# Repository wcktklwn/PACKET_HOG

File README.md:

# PACKET_HOG

10-node ESP32-C5 scanner carrier board. One master, a bank of scan nodes, single USB-C power in.

Status: **PacketHog-V2 first batch is sold out. A restock order has been placed** (no firm arrival date, no preorders; the store page reopens when boards are in hand). V1 (first batch of 8) is also sold out. Every V2 board is assembled and checked before it ships.

## What it is

Packet Hog C5 is a carrier board built around the Seeed XIAO ESP32-C5. One master node coordinates a bank of scanner nodes over ESP-NOW, each scanning dual-band Wi-Fi (2.4/5 GHz) and BLE. The whole array runs off a single USB-C input.

Built deliberately barebones with power distribution, node bank, antenna breakout, nothing else.

Board size: 183.7mm x 121.1mm (7.23 x 4.77 in), 1.6mm thick. Standard case: 188.1mm x 125.5mm, about 29mm tall. Fan case: about 45.5mm tall.

## Buy it

PacketHog-V2: **$100**, shipping to the US only right now. Same price for every option. **Currently sold out, restock ordered.** Restock alert signup: [tally.so/r/Z9Elga](https://tally.so/r/Z9Elga)

[fusedstamen.com/packethogv2](https://fusedstamen.com/packethogv2)

Options at checkout when available: soldered RP-SMA connectors, or bare board (as received from assembly, SMA positions empty). Every board comes with the standard printed case. A case with a 30mm fan opening is available to print from this repo if you want one. Name and Discord are optional at checkout; I only need a shipping address and email.

Modules (Seeed XIAO ESP32-C5), antennas and fan not included. Outside the US, message me on Discord first - import VAT, duties and carrier fees are paid by the buyer on delivery.

## Case hardware

- Standard case: 4x M3x25 screws into M3 heat-set inserts.
- Fan case lid: 4x M3x40 (about 2.5mm of thread engagement; use M3x45 if it feels loose).
- Fan: 5V, 2-pin, 30mm. Check the fan thickness against the fan case. Fan screws are 2-4x M3x8 to M3x10 self-tapping. Specific fans are untested.

**Note on the RP-SMA connectors (J1-J10):** they're mounted to the board for physical support only - there's no PCB trace routing antenna signal to them. Each node module's signal reaches its SMA connector through a short U.FL-to-RP-SMA pigtail from the module itself, not through the board's copper. Same setup as the Piglet, in case that's caused confusion before.

**Mounting orientation:** every header position follows the same rule. Seat each XIAO module so its USB-C port faces the same side as the nearby capacitor (e.g. C11 sits next to the H1A/H1B pair) - that side matches the direction the onboard USB-C (J11) faces. The module's U.FL antenna pad ends up on the opposite side. Get this backwards and the module won't seat or power on correctly; double check before powering on.

## Version history

- **Prototype 1** - First routed prototype. Had a wiring mistake around the CH224K USB-C PD negotiation chip: on a "smart" PD-negotiating charger, the board could get handed the wrong voltage, which risked damaging the nodes. Safe with plain 5V "dumb" chargers only.
- **Prototype 2** - CH224K removed entirely; replaced with 5.1kΩ pull-down resistors on CC1/CC2, forcing 5V-default behavior regardless of charger. Also added reverse-polarity protection, a fuse at the power input, bulk + per-node decoupling capacitors, and 10 edge-mounted SMA connectors for external antennas. Had a layout flaw: SMA connector mounts sat too close to the header pins, leaving insufficient clearance to hand-solder/route pigtail connections without crowding the header footprints. Also shipped without mounting holes, so boards couldn't be securely fastened into a case.
- **PacketHog-V1** - Fixes the clearance flaw by widening the board (77.1mm to 121.1mm) to give proper spacing between the SMA connectors and the header rows. Added M3 mounting holes. Rounded board corners. SMA connectors hand-soldered (not PCBA-populated). First batch of 8 sold out.
- **PacketHog-V2** - Current revision. Power traces widened from 0.5mm to 1.0mm (the USB-C-to-fuse run is limited by the connector pad width). Added a 2-pin fan header (5V + GND, factory assembled). Added an AUX 5V/GND through-hole header, unpopulated, same pinout as the fan header (square pad GND, round pad +5V). Added 7 labelled test points: USB input voltage, between fuse and diode, 5V rail, far-end 5V, and 3x GND. Silkscreen cleanup; back label says V2. Power parts unchanged from V1. Still hand-soldered through-hole RP-SMA (mechanical only), plain USB-C 5V with no PD, 3A maximum (PTC fuse, fan counts against it).
- **Planned for V3** - Power switch, power LED, onboard U.FL plus edge SMA, battery input, possibly 4-layer.

**Known issue:** some nodes drop out with certain off-brand USB cables or power banks. Cause not yet measured; V2 does not claim to fix it. Use a decent USB-C cable and a supply that can deliver 5V at 3A.

## PacketHog-20

Unreleased 20-socket layout in `hardware/PacketHog-20/`. PacketHog-V2 above is unchanged and is still the board for sale. This board has not been fabricated or powered.

20 XIAO ESP32-C5 sockets, 2 rows of 10. Nodes 1–10 run along the top edge and 11–20 along the bottom, on the same 35 mm SMA pitch as V2. Board size: 432.05 mm × 86.10 mm (17.01 × 3.39 in), 1.6 mm thick, 2-layer, 1 oz. Corners are rounded at a 3 mm radius. The V2 case does not fit, and there is no case for this board. Seat each module the same way as V2: USB-C toward the nearby capacitor, the same direction the board USB connector (J21) faces. V2 fits a U.FL beside each SMA and a short trace between the center pins. This board leaves that connector and that trace off. The antenna is still the module's own U.FL and a pigtail to the SMA.

The USB-C input is the V2 circuit, shifted to the right edge: 5.1 kΩ on CC1/CC2, series Schottky, PTC fuse. That path cannot feed 20 radios. The high-current input is J22, a Phoenix MKDS 1,5/2-5.08 screw terminal on the left. Square pad is GND, round pad is VIN, and the wire openings face the board edge. F2 is a Littelfuse 0451010, a 10 A very-fast Nano2 fuse, in series with Q1, an onsemi NTMFS002P03P8Z P-channel MOSFET. Its Rds(on) maximum is 2.3 mΩ at Vgs = −4.5 V, about 18 mV and 0.15 W at 8 A using that datasheet maximum. The package is CASE 506EZ. The footprint on the board is the library SO-8 FL land ONSemi_SO-8FL_488AA, which matches the 506EZ recommended land. The exposed drain pad is not a hand-solder package.

Q2, an MMBT3904, pulls the gate down only while the fused input is present, so the FET turns on for the screw terminal and stays off when only USB is connected. USB then cannot backfeed into J22, and the USB Schottky stays reverse-biased while the FET drop is tens of millivolts. D4, a BZT52C12, clamps the gate-source voltage. It does not clamp the input. The body diode and the channel both pass a higher VIN onto the 5 V rail. The silk says 5V ONLY. A 12 V supply on J22 would destroy the modules. Reverse polarity on J22 leaves the FET off.

The screw terminal, the USB input, and the buck share an unswitched +5V island. On the back of the inlet that tie is 2.8 mm. It has not been measured at the array current. Q7, another NTMFS002P03P8Z, connects the island to the load net. Its source is the island and its drain is the load, so the body diode does not run the radios when the FET is off. From there a 2.8 mm spine feeds a 4.0 mm bus along the top, ending at x = 419.50 mm, and a 3.2 mm bus along the bottom, from the bulk capacitor at x = 77.70 mm to x = 413.50 mm. A rough IPC-2221 figure for 10 A on 1 oz external copper at a 20 °C rise is about 4.6 mm, and the spine stays 2.8 mm because the header pins sit next to it. An estimate of simultaneous transmit, about 0.44 A per node at 5 V, is about 8.9 A. The spine and the 8 A buck below are sized under that estimate. An average scan is far below simultaneous transmit. None of this drop or heating has been measured.

SW1 is a C&K JS202011CQN, a maintained DPDT slide switch. One pole grounds Q7's gate in the ON position. R23, 100 kΩ to the island, holds the gate up when that pole is open, so the FET stays off. The other pole grounds the base of Q8, an MMBT3904, in the ON position. When the switch is open, R22, 100 kΩ from the pack, turns Q8 on and holds the buck enable low. The switch carries gate and base current, not the radio current. Charging stays on the fused input and continues while the radios are off. USB is on the island side of Q7, so the board USB does not run the radios with the switch open either. The silk says ON on the wired throw. The C&K pin drawing was not available, so that direction has not been checked. If the slider is backwards, both positions still exist and the silk names the one that is wired on. Q7 uses the same 2.3 mΩ maximum, about 18 mV and 0.15 W at 8 A from that datasheet figure. That drop has not been measured. The switch does not clamp the input. The inlet silk still says 5V ONLY.

The pack is external: a 2S Li-ion pack with its own BMS, plugged into J23, an XT30PW-M. Onboard 18650 holders were rejected. One cell cannot supply the array at 5 V, and a holder adds reverse insertion and height. Library silk marks J23 pad 2 as + and pad 1 as −. That marking is the library silk and has not been checked against the AMASS drawing. Confirm it before building a cable. J24 is a JST XH B3B-XH-A balance header. Pin 1 is pack−, pin 2 is the mid-cell sense, and pin 3 is cell+ on the cell side of Q3, the same node as J23 pad 2. The balance plug is a sense connection for the charger. It is not pack protection, and pin 3 must stay on the cell side of Q3 so the cable does not bypass the reverse-polarity FET.

Q3, another NTMFS002P03P8Z, has its drain toward the pack and its source on the protected PACK rail. A reversed pack leaves the FET off. A correct pack bootstraps through the body diode and the FET turns on. This does not clamp the pack voltage.

U1 is an Injoinic IP2326 boost charger. It charges the pack from the fused screw-terminal input (VIN_F). With the adapter unplugged the charger input is open, so the buck cannot feed the charger. Charge current is about 1 A (90.9 kΩ on ISET). The charge timer is 12 h (120 kΩ on TIME_SET), so a larger pack can hit the timeout and stop early. The NTC pin is a fixed 51 kΩ to ground, not a cell thermistor. CON_SEL and VSET are open, which selects 2S and 8.4 V. The datasheet application note's series 0.5 Ω on VIN is omitted, and so is the balance-bleed resistor. The pack BMS does the balance bleed. A 1 A charge into 2S is on the order of 2 A from the 5 V input. That current shares F2 with the radios. Full transmit while charging sits at the 10 A hold rating of the fuse.

U2 is a TI TPS56837 8 A synchronous buck, 500 kHz, set to about 5.0 V (73.2 kΩ / 10.0 kΩ). Q4 connects the buck onto the unswitched island through another P-channel FET, and Q5 holds the buck off while the adapter is present, so the adapter runs the radios and the charger fills the pack. Q8 does that same hold from the pack while SW1 is open, so an unloaded buck does not drain the pack with the radios off. The enable pin is held by those transistors. Its absolute maximum is 6 V, so it stays off the pack. The 5 V output needs the pack above about 5.5 V. The pack BMS should cut the pack off before that. TI's thermal numbers are from a 4-layer evaluation board. This board is 2-layer 1 oz, so 8 A continuous will run hotter. That has not been measured.

On J21 the four stacked GND lands, A1, A12, B1, and B12, are 1.08 mm long. GCT's recommended land is 1.15 mm. Each land is 0.07 mm shorter on the end next to the Ø0.65 locating peg, and the far end stays on the datasheet coordinate, so those holes meet the 0.25 mm clearance rule. The signal and VBUS pads stay at 1.15 mm. PacketHog-V2 still uses the 1.15 mm lands, so J11 still has those four hole-clearance errors.

The ground zone was refilled in KiCad 10.0.8 on 2026-11-17, after the onboard U.FL connectors were removed. DRC reports no unconnected nets, no errors, and no warnings. The V2 back logo was removed. Shifted onto this outline it covered the top-row connectors. The schematic in that folder is still the 10-node drawing. Do not update the PCB from it. The PCB is the netlist.

## Status of what's tested

| Component | Status |
|---|---|
| Power distribution | Tested |
| Fully populated board scanning | Tested |
| PacketHog-V1 board fab/assembly | Tested |
| PacketHog-V2 board fab/assembly | Tested (each board checked before shipping) |
| Fan case (30mm) | Complete, files in this repo |
| Antenna path (module -> U.FL/SMA pigtail) | Tested |

## Thermal notes

I ran a thermal test on a V1 board in a closed case in a room at about 78F (25.5C). After 75+ minutes of running, the air inside the case levelled off around 96F (36C) and the nodes measured about 102-110F (39-43C) with a thermocouple. An IR thermometer read higher, 108-118F (42-48C), which is typical of IR on shiny surfaces, so treat the thermocouple numbers as the more reliable set. The test was on V1; V2 uses the same power parts with wider copper.

For reference, Espressif rates the ESP32-C5 modules for an operating ambient temperature of -40C to 85C (185F). The Seeed XIAO ESP32-C5 board is listed at 0C to 85C. Nodes ran well inside that range in my test, so I don't think a fan is necessary. The fan header and fan case are there if you want extra airflow or plan to run in a hot environment, such as a car parked in the sun. Those limits are ambient ratings, so a very hot environment leaves less margin.

Test data: [Packet_Hog-v1-Thermal_Testing.xlsx](./Packet_Hog-v1-Thermal_Testing.xlsx)

## License

Licensed under **CC BY-NC 4.0** - see [LICENSE](./LICENSE) for full terms.

Short version: you're free to build one for yourself and modify it for personal, non-commercial use. Selling anything built from this design - boards, kits, or products - requires explicit permission from me first. See the LICENSE file for exactly what that means.

## Contact

- Discord: `Fusedstamen`
- GitHub: [github.com/FusedStamen](https://github.com/FusedStamen)

If you want to use this commercially, reach out through one of the above. Don't assume permission - wait for a yes.

## Name

"Packet Hog" - a reference to [Bilmuri](https://bilmuri.com), not a fork or rename of anyone else's project.

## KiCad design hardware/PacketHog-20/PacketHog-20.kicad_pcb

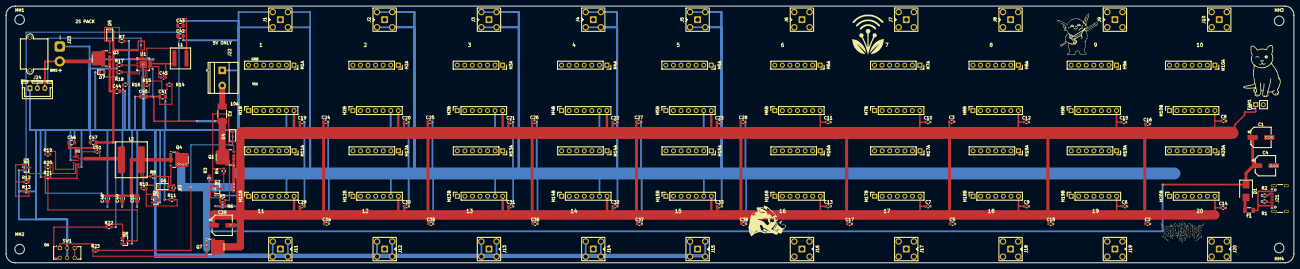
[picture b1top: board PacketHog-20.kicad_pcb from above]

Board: 2 copper layers, 432.1 x 86.1 mm, 163 parts (0 on the bottom side), 38 nets.

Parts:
C1, C4, C39: CP_Elec_6.3x5.4
C2, C3, C5, C16, C17, C18, C24, C25, C26, C27, C28, C34, C35, C36, C37, C38: 1uF; C_0603_1608Metric
C6, C7, C8, C9, C10, C11, C12, C13, C14, C15, C19, C20, C21, C22, C23, C29, C30, C31, C32, C33: 10uF; C_0603_1608Metric
C40, C41, C44, C46, C47: 10uF 25V; C_0805_2012Metric
C42, C43, C48, C49, C50: 22uF 25V; C_0805_2012Metric
C45, C51: 100nF; C_0603_1608Metric
D1: D_SMB
D4, D5, D6: BZT52C12; D_SOD-123
D7: RED; LED_0603_1608Metric
F1: Fuse_1206_3216Metric
F2: 0451010; Fuse_Littelfuse-NANO2-451_453
FAN1: PinHeader_1x02_P2.54mm_Vertical
H1A, H1B, H2A, H2B, H3A, H3B, H4A, H4B, H5A, H5B, H6A, H6B, H7A, H7B, H8A, H8B, H9A, H9B, H10A, H10B, H11A, H11B, H12A, H12B, H13A, H13B, H14A, H14B, H15A, H15B, H16A, H16B, H17A, H17B, H18A, H18B, H19A, H19B, H20A, H20B: PinSocket_1x07_P2.54mm_Vertical
J1, J2, J3, J4, J5, J6, J7, J8, J9, J10, J11, J12, J13, J14, J15, J16, J17, J18, J19, J20: SMA_BAT_Wireless_BWSMA-KWE-Z001
J21: USB_C_Receptacle_GCT_USB4105; USB_C_Receptacle_GCT_USB4105-xx-A_16P_TopMnt_Horizontal
J22: MKDS-1,5/2-5.08; TerminalBlock_Phoenix_MKDS-1,5-2-5.08_1x02_P5.08mm_Horizont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
J23: XT30PW-M; AMASS_XT30PW-M_1x02_P2.50mm_Horizontal
J24: B3B-XH-A; JST_XH_B3B-XH-A_1x03_P2.50mm_Vertical
L1: XAL6030-222MEC; L_Coilcraft_XAL6030-XXX
L2: XAL1010-332MED; L_Coilcraft_XAL1010-XXX
MH1, MH2, MH3, MH4: MountingHole_3.2mm_M3
Q1, Q3, Q4, Q7: NTMFS002P03P8Z; ONSemi_SO-8FL_488AA
Q2, Q5, Q6, Q8: MMBT3904; SOT-23
R1, R2, R14: 5.1k; R_0603_1608Metric
R3, R6, R7, R8, R11, R12, R13, R22, R23: 100k; R_0603_1608Metric
R4, R9: 1k; R_0603_1608Metric
R5, R10: 47k; R_0603_1608Metric
R15: 90.9k; R_0603_1608Metric
R16: 120k; R_0603_1608Metric
R17: 51k; R_0603_1608Metric
R18: 100; R_0603_1608Metric
R19: 30.1k; R_0603_1608Metric
R20: 73.2k; R_0603_1608Metric
R21: 10.0k; R_0603_1608Metric
SW1: JS202011CQN; SW_CK_JS202011CQN_DPDT_Straight
U1: IP2326; QFN-24-1EP_4x4mm_P0.5mm_EP2.5x2.5mm
U2: TPS56837; TPS56837_RPA0010A

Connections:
+5V: C1.1, C4.1, D1.1, D4.1, Q1.1, Q1.2, Q1.3, Q4.5, Q7.1, Q7.2, Q7.3, R3.2, R23.2
+5V_SW: C2.1, C3.1, C5.1, C6.1, C7.1, C8.1, C9.1, C10.1, C11.1, C12.1, C13.1, C14.1, C15.1, C16.1, C17.1, C18.1, C19.1, C20.1, C21.1, C22.1, C23.1, C24.1, C25.1, C26.1, C27.1, C28.1, C29.1, C30.1, C31.1, C32.1, C33.1, C34.1, C35.1, C36.1, C37.1, C38.1, C39.1, FAN1.1, H1B.7, H2B.7, H3B.7, H4B.7, H5B.7, H6B.7, H7B.7, H8B.7, H9B.7, H10B.7, H11B.7, H12B.7, H13B.7, H14B.7, H15B.7, H16B.7, H17B.7, H18B.7, H19B.7, H20B.7, Q7.5
BUCK5: C48.2, C49.2, C50.2, D6.1, L2.2, Q4.1, Q4.2, Q4.3, R8.1, R10.1, R20.1
BUCK_BOOT: C51.1, U2.7
BUCK_EN: Q5.3, Q8.3, U2.1
BUCK_FB: R20.2, R21.2, U2.2
BUCK_MODE: R19.2, U2.10
BUCK_SW: C51.2, L2.1, U2.6
CC1: J21.B5, R2.2
CC2: J21.A5, R1.2
CHG_BST: C45.1, U1.14
CHG_EN: R14.1, U1.12
CHG_ISET: R15.2, U1.11
CHG_LED: R18.2, U1.6
CHG_LX: C45.2, L1.1, U1.15, U1.16, U1.17
CHG_NTC: R17.2, U1.4
CHG_TIME: R16.2, U1.7
CHG_VSYS: C42.1, C43.1, L1.2, U1.19, U1.20
F1_OUT: D1.2, F1.2
GATE: D4.2, Q1.4, R3.1, R4.2
GATE3: D5.2, Q3.4, R7.1
GATE4: D6.2, Q4.4, R8.2, R9.2
GATE7: Q7.4, R23.1, SW1.1
GND: C1.2, C2.2, C3.2, C4.2, C5.2, C6.2, C7.2, C8.2, C9.2, C10.2, C11.2, C12.2, C13.2, C14.2, C15.2, C16.2, C17.2, C18.2, C19.2, C20.2, C21.2, C22.2, C23.2, C24.2, C25.2, C26.2, C27.2, C28.2, C29.2, C30.2, C31.2, C32.2, C33.2, C34.2, C35.2, C36.2, C37.2, C38.2, C39.2, C40.1, C41.2, C42.2, C43.2, C44.2, C46.2, C47.1, C48.1, C49.1, C50.1, D7.1, FAN1.2, H1B.6, H2B.6, H3B.6, H4B.6, H5B.6, H6B.6, H7B.6, H8B.6, H9B.6, H10B.6, H11B.6, H12B.6, H13B.6, H14B.6, H15B.6, H16B.6, H17B.6, H18B.6, H19B.6, H20B.6, J1.2, J2.2, J3.2, J4.2, J5.2, J6.2, J7.2, J8.2, J9.2, J10.2, J11.2, J12.2, J13.2, J14.2, J15.2, J16.2, J17.2, J18.2, J19.2, J20.2, J21.A1, J21.A12, J21.B1, J21.B12, J21.SH, J22.1, J23.1, J24.1, Q2.2, Q5.2, Q6.2, Q8.2, R1.1, R2.1, R6.1, R7.2, R11.1, R13.1, R15.1, R16.1, R17.1, R19.1, R21.1, SW1.2, SW1.5, U1.18, U1.24, U1.25, U2.3, U2.9
LED_A: D7.2, R18.1
PACK: C44.1, C46.1, C47.2, D5.1, Q3.1, Q3.2, Q3.3, R22.2, U1.21, U1.22, U2.8
PACK_IN: J23.2, J24.3, Q3.5
Q2B: Q2.1, R5.1, R6.2
Q2C: Q2.3, R4.1
Q5B: Q5.1, R12.1, R13.2
Q6B: Q6.1, R10.2, R11.2
Q6C: Q6.3, R9.1
Q8B: Q8.1, R22.1, SW1.6
SW_NC: SW1.3, SW1.4
VBATM: J24.2, U1.23
VBUS: F1.1, J21.A4, J21.A9, J21.B4, J21.B9
VIN: F2.1, J22.2
VIN_F: C40.2, C41.1, F2.2, Q1.5, R5.2, R12.2, R14.2, U1.13

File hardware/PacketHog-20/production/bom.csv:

Value,Footprint,Quantity,Designators
0451010,Fuse:Fuse_Littelfuse-NANO2-451_453,1,"F2"
10.0k,Resistor_SMD:R_0603_1608Metric,1,"R21"
100,Resistor_SMD:R_0603_1608Metric,1,"R18"
100k,Resistor_SMD:R_0603_1608Metric,9,"R11 R12 R13 R22 R23 R3 R6 R7 R8"
100nF,Capacitor_SMD:C_0603_1608Metric,2,"C45 C51"
10uF,Capacitor_SMD:C_0603_1608Metric,20,"C10 C11 C12 C13 C14 C15 C19 C20 C21 C22 C23 C29 C30 C31 C32 C33 C6 C7 C8 C9"
10uF 25V,Capacitor_SMD:C_0805_2012Metric,5,"C40 C41 C44 C46 C47"
120k,Resistor_SMD:R_0603_1608Metric,1,"R16"
1k,Resistor_SMD:R_0603_1608Metric,2,"R4 R9"
1uF,Capacitor_SMD:C_0603_1608Metric,16,"C16 C17 C18 C2 C24 C25 C26 C27 C28 C3 C34 C35 C36 C37 C38 C5"
22uF 25V,Capacitor_SMD:C_0805_2012Metric,5,"C42 C43 C48 C49 C50"
30.1k,Resistor_SMD:R_0603_1608Metric,1,"R19"
47k,Resistor_SMD:R_0603_1608Metric,2,"R10 R5"
5.1k,Resistor_SMD:R_0603_1608Metric,3,"R1 R14 R2"
51k,Resistor_SMD:R_0603_1608Metric,1,"R17"
73.2k,Resistor_SMD:R_0603_1608Metric,1,"R20"
90.9k,Resistor_SMD:R_0603_1608Metric,1,"R15"
B3B-XH-A,Connector_JST:JST_XH_B3B-XH-A_1x03_P2.50mm_Vertical,1,"J24"
BZT52C12,Diode_SMD:D_SOD-123,3,"D4 D5 D6"
CP_Elec_6.3x5.4,Capacitor_SMD:CP_Elec_6.3x5.4,3,"C1 C39 C4"
D_SMB,Diode_SMD:D_SMB,1,"D1"
Fuse_1206_3216Metric,Fuse:Fuse_1206_3216Metric,1,"F1"
IP2326,Package_DFN_QFN:QFN-24-1EP_4x4mm_P0.5mm_EP2.5x2.5mm,1,"U1"
JS202011CQN,Button_Switch_THT:SW_CK_JS202011CQN_DPDT_Straight,1,"SW1"
MKDS-1,5/2-5.08,TerminalBlock_Phoenix:TerminalBlock_Phoenix_MKDS-1,5-2-5.08_1x02_P5.08mm_Horizontal,1,"J22"
MMBT3904,Package_TO_SOT_SMD:SOT-23,4,"Q2 Q5 Q6 Q8"
MountingHole_3.2mm_M3,MountingHole:MountingHole_3.2mm_M3,4,"MH1 MH2 MH3 MH4"
NTMFS002P03P8Z,PacketHog20:ONSemi_SO-8FL_488AA,4,"Q1 Q3 Q4 Q7"
PinHeader_1x02_P2.54mm_Vertical,Connector_PinHeader_2.54mm:PinHeader_1x02_P2.54mm_Vertical,1,"FAN1"
PinSocket_1x07_P2.54mm_Vertical,Connector_PinSocket_2.54mm:PinSocket_1x07_P2.54mm_Vertical,40,"H10A H10B H11A H11B H12A H12B H13A H13B H14A H14B H15A H15B H16A H16B H17A H17B H18A H18B H19A H19B H1A H1B H20A H20B H2A H2B H3A H3B H4A H4B H5A H5B H6A H6B H7A H7B H8A H8B H9A H9B"
RED,LED_SMD:LED_0603_1608Metric,1,"D7"
SMA_BAT_Wireless_BWSMA-KWE-Z001,Connector_Coaxial:SMA_BAT_Wireless_BWSMA-KWE-Z001,20,"J1 J10 J11 J12 J13 J14 J15 J16 J17 J18 J19 J2 J20 J3 J4 J5 J6 J7 J8 J9"
TPS56837,PacketHog20:TPS56837_RPA0010A,1,"U2"
USB_C_Receptacle_GCT_USB4105,PacketHog20:USB_C_Receptacle_GCT_USB4105-xx-A_16P_TopMnt_Horizontal,1,"J21"
XAL1010-332MED,Inductor_SMD:L_Coilcraft_XAL1010-XXX,1,"L2"
XAL6030-222MEC,Inductor_SMD:L_Coilcraft_XAL6030-XXX,1,"L1"
XT30PW-M,Connector_AMASS:AMASS_XT30PW-M_1x02_P2.50mm_Horizontal,1,"J23"

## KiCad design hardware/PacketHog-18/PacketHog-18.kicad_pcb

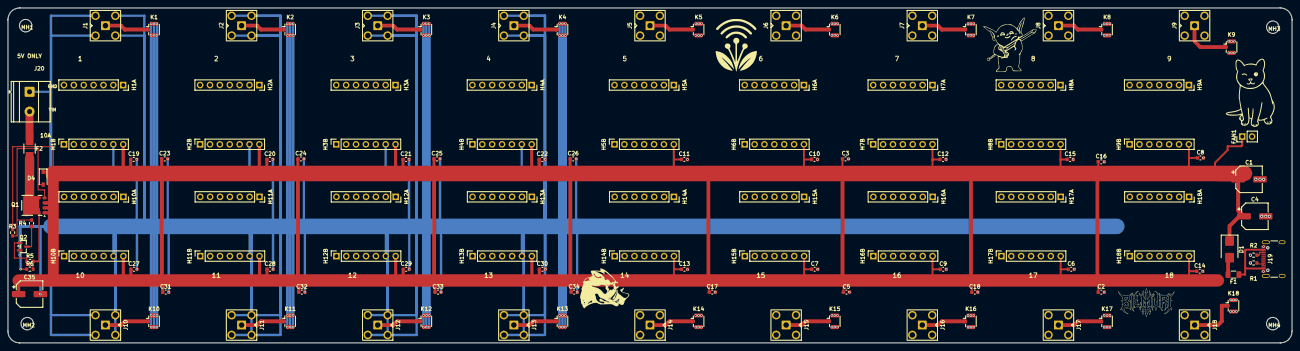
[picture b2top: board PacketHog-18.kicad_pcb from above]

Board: 2 copper layers, 330.1 x 86.1 mm, 126 parts (0 on the bottom side), 29 nets.

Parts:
C1, C4, C35: CP_Elec_6.3x5.4
C2, C3, C5, C16, C17, C18, C23, C24, C25, C26, C31, C32, C33, C34: 1uF; C_0603_1608Metric
C6, C7, C8, C9, C10, C11, C12, C13, C14, C15, C19, C20, C21, C22, C27, C28, C29, C30: 10uF; C_0603_1608Metric
D1: D_SMB
D4: BZT52C12; D_SOD-123
F1: Fuse_1206_3216Metric
F2: 0451010; Fuse_Littelfuse-NANO2-451_453
FAN1: PinHeader_1x02_P2.54mm_Vertical
H1A, H1B, H2A, H2B, H3A, H3B, H4A, H4B, H5A, H5B, H6A, H6B, H7A, H7B, H8A, H8B, H9A, H9B, H10A, H10B, H11A, H11B, H12A, H12B, H13A, H13B, H14A, H14B, H15A, H15B, H16A, H16B, H17A, H17B, H18A, H18B: PinSocket_1x07_P2.54mm_Vertical
J1, J2, J3, J4, J5, J6, J7, J8, J9, J10, J11, J12, J13, J14, J15, J16, J17, J18: SMA_BAT_Wireless_BWSMA-KWE-Z001
J19: USB_C_Receptacle_GCT_USB4105; USB_C_Receptacle_GCT_USB4105-xx-A_16P_TopMnt_Horizontal
J20: MKDS-1,5/2-5.08; TerminalBlock_Phoenix_MKDS-1,5-2-5.08_1x02_P5.08mm_Horizont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
K1, K2, K3, K4, K5, K6, K7, K8, K9, K10, K11, K12, K13, K14, K15, K16, K17, K18: U.FL_Hirose_U.FL-R-SMT-1_Vertical
MH1, MH2, MH3, MH4: MountingHole_3.2mm_M3
Q1: NTMFS002P03P8Z; ONSemi_SO-8FL_488AA
Q2: MMBT3904; SOT-23
R1, R2: 5.1k; R_0603_1608Metric
R3, R6: 100k; R_0603_1608Metric
R4: 1k; R_0603_1608Metric
R5: 47k; R_0603_1608Metric

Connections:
+5V: C1.1, C2.1, C3.1, C4.1, C5.1, C6.1, C7.1, C8.1, C9.1, C10.1, C11.1, C12.1, C13.1, C14.1, C15.1, C16.1, C17.1, C18.1, C19.1, C20.1, C21.1, C22.1, C23.1, C24.1, C25.1, C26.1, C27.1, C28.1, C29.1, C30.1, C31.1, C32.1, C33.1, C34.1, C35.1, D1.1, D4.1, FAN1.1, H1B.7, H2B.7, H3B.7, H4B.7, H5B.7, H6B.7, H7B.7, H8B.7, H9B.7, H10B.7, H11B.7, H12B.7, H13B.7, H14B.7, H15B.7, H16B.7, H17B.7, H18B.7, Q1.1, Q1.2, Q1.3, R3.2
CC1: J19.B5, R2.2
CC2: J19.A5, R1.2
F1_OUT: D1.2, F1.2
GATE: D4.2, Q1.4, R3.1, R4.2
GND: C1.2, C2.2, C3.2, C4.2, C5.2, C6.2, C7.2, C8.2, C9.2, C10.2, C11.2, C12.2, C13.2, C14.2, C15.2, C16.2, C17.2, C18.2, C19.2, C20.2, C21.2, C22.2, C23.2, C24.2, C25.2, C26.2, C27.2, C28.2, C29.2, C30.2, C31.2, C32.2, C33.2, C34.2, C35.2, FAN1.2, H1B.6, H2B.6, H3B.6, H4B.6, H5B.6, H6B.6, H7B.6, H8B.6, H9B.6, H10B.6, H11B.6, H12B.6, H13B.6, H14B.6, H15B.6, H16B.6, H17B.6, H18B.6, J1.2, J2.2, J3.2, J4.2, J5.2, J6.2, J7.2, J8.2, J9.2, J10.2, J11.2, J12.2, J13.2, J14.2, J15.2, J16.2, J17.2, J18.2, J19.A1, J19.A12, J19.B1, J19.B12, J19.SH, J20.1, K1.2, K2.2, K3.2, K4.2, K5.2, K6.2, K7.2, K8.2, K9.2, K10.2, K11.2, K12.2, K13.2, K14.2, K15.2, K16.2, K17.2, K18.2, Q2.2, R1.1, R2.1, R6.1
Q2B: Q2.1, R5.1, R6.2
Q2C: Q2.3, R4.1
SMA1: J1.1, K1.1
SMA2: J2.1, K2.1
SMA3: J3.1, K3.1
SMA4: J4.1, K4.1
SMA5: J5.1, K5.1
SMA6: J6.1, K6.1
SMA7: J7.1, K7.1
SMA8: J8.1, K8.1
SMA9: J9.1, K9.1
SMA10: J10.1, K10.1
SMA11: J11.1, K11.1
SMA12: J12.1, K12.1
SMA13: J13.1, K13.1
SMA14: J14.1, K14.1
SMA15: J15.1, K15.1
SMA16: J16.1, K16.1
SMA17: J17.1, K17.1
SMA18: J18.1, K18.1
VBUS: F1.1, J19.A4, J19.A9, J19.B4, J19.B9
VIN: F2.1, J20.2
VIN_F: F2.2, Q1.5, R5.2

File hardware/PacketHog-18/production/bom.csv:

Value,Footprint,Quantity,Designators
0451010,Fuse:Fuse_Littelfuse-NANO2-451_453,1,"F2"
100k,Resistor_SMD:R_0603_1608Metric,2,"R3 R6"
10uF,Capacitor_SMD:C_0603_1608Metric,18,"C10 C11 C12 C13 C14 C15 C19 C20 C21 C22 C27 C28 C29 C30 C6 C7 C8 C9"
1k,Resistor_SMD:R_0603_1608Metric,1,"R4"
1uF,Capacitor_SMD:C_0603_1608Metric,14,"C16 C17 C18 C2 C23 C24 C25 C26 C3 C31 C32 C33 C34 C5"
47k,Resistor_SMD:R_0603_1608Metric,1,"R5"
5.1k,Resistor_SMD:R_0603_1608Metric,2,"R1 R2"
BZT52C12,Diode_SMD:D_SOD-123,1,"D4"
CP_Elec_6.3x5.4,Capacitor_SMD:CP_Elec_6.3x5.4,3,"C1 C35 C4"
D_SMB,Diode_SMD:D_SMB,1,"D1"
Fuse_1206_3216Metric,Fuse:Fuse_1206_3216Metric,1,"F1"
MKDS-1,5/2-5.08,TerminalBlock_Phoenix:TerminalBlock_Phoenix_MKDS-1,5-2-5.08_1x02_P5.08mm_Horizontal,1,"J20"
MMBT3904,Package_TO_SOT_SMD:SOT-23,1,"Q2"
MountingHole_3.2mm_M3,MountingHole:MountingHole_3.2mm_M3,4,"MH1 MH2 MH3 MH4"
NTMFS002P03P8Z,Package_SO:ONSemi_SO-8FL_488AA,1,"Q1"
PinHeader_1x02_P2.54mm_Vertical,Connector_PinHeader_2.54mm:PinHeader_1x02_P2.54mm_Vertical,1,"FAN1"
PinSocket_1x07_P2.54mm_Vertical,Connector_PinSocket_2.54mm:PinSocket_1x07_P2.54mm_Vertical,36,"H10A H10B H11A H11B H12A H12B H13A H13B H14A H14B H15A H15B H16A H16B H17A H17B H18A H18B H1A H1B H2A H2B H3A H3B H4A H4B H5A H5B H6A H6B H7A H7B H8A H8B H9A H9B"
SMA_BAT_Wireless_BWSMA-KWE-Z001,Connector_Coaxial:SMA_BAT_Wireless_BWSMA-KWE-Z001,18,"J1 J10 J11 J12 J13 J14 J15 J16 J17 J18 J2 J3 J4 J5 J6 J7 J8 J9"
U.FL_Hirose_U.FL-R-SMT-1_Vertical,Connector_Coaxial:U.FL_Hirose_U.FL-R-SMT-1_Vertical,18,"K1 K10 K11 K12 K13 K14 K15 K16 K17 K18 K2 K3 K4 K5 K6 K7 K8 K9"
USB_C_Receptacle_GCT_USB4105,Connector_USB:USB_C_Receptacle_GCT_USB4105-xx-A_16P_TopMnt_Horizontal,1,"J19"

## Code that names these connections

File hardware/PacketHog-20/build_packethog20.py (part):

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def _route_battery(board):
    """Copper for the bay. Endpoints come from the pads; corners are explicit."""
    t = []
    # --- pack positive into Q3 drain, and the balance cell+ pin ---
    xt = _p(board, "J23", "2")
    drain = _p(board, "Q3", "5")
    t += wire([xt, (drain[0], xt[1]), drain], 1.2, "PACK_IN")
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    # crossing this rail. The wide copper stops outside that slot.
    t += wire([(pack_x, 69.2), (52.3, 69.2)], 0.8, "PACK")
    t += wire([(52.3, 69.2), (52.3, 66.2), (54.4, 66.2), (54.4, 69.2)], 0.4, "PACK")
    # The VBATM stub leaves pin 23 at x=53.25. A 0.4 mm finish on the VOUT pin
    # (x=53.75) is 0.175 mm from that stub. 0.25 mm leaves a 0.25 mm gap.
    t += wire([(54.4, 69.2), (vout[0], 69.2), (vout[0], 70.6), vout], 0.25, "PACK")
    vout2 = _p(board, "U1", "21")
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    tie_x = lx_pins[0][0] + 0.75
    for p in lx_pins:
        t += wire([p, (tie_x, p[1])], 0.25, "CHG_LX")
    t += wire([(tie_x, lx_pins[0][1]), (tie_x, lx_pins[-1][1])], 0.25, "CHG_LX")
    l1_lx = _p(board, "L1", "1")
    t += wire([(tie_x, lx_pins[1][1]), (l1_lx[0], lx_pins[1][1]), l1_lx], 0.5, "CHG_LX")
    bst = _p(board, "U1", "14")
    c45a = _p(board, "C45", "1")
    c45b = _p(board, "C45", "2")
    # Right of the VIN pin, and it stops above the EN run.
    t += wire([bst, (59.2, bst[1]), (59.2, c45a[1]), c45a], 0.25, "CHG_BST")
    t += wire([c45b, (c45b[0], lx_pins[1][1])], 0.25, "CHG_LX")
    vsys_pins = [_p(board, "U1", "19"), _p(board, "U1", "20")]
    t += wire([(vsys_pins[0][0], 71.85), (vsys_pins[1][0], 71.85)], 0.25, "CHG_VSYS")
    l1_vs = _p(board, "L1", "2")
    # Above both inductor pads. y=70.35 crosses the LX pad (it spans y 69.25–74.75).
    # The pin escape stays 0.25 mm so it does not widen past pin 19 toward PGND.
    t += wire([vsys_pins[0], (vsys_pins[0][0], 68.6)], 0.25, "CHG_VSYS")
    t += wire([(vsys_pins[0][0], 68.6), (l1_vs[0], 68.6)], 0.4, "CHG_VSYS")
    # Each cap's ground pad sits between its VSYS pad and L1. Leave upward,
    # then join the drop on the VSYS pad's own x.
    c42 = _p(board, "C42", "1")
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    c41 = _p(board, "C41", "1")
    vin = _p(board, "U1", "13")
    t += wire([(72.0, f2[1]), (57.6, f2[1]), (57.6, c40[1]), c40, c41], 0.5, "VIN_F")
    # The pin cannot drop on F.Cu: CHG_EN owns y=79.6 and BST owns x=59.2.
    # The BST run is 0.5 mm above this pin, so the via sits below the stub
    # (a via on the pin row is 0.075 mm from that trace). Hop at x=57.2,
    # off lane 58, and return on the cap row.
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    t += wire([d6k, (d6k[0], 114.6), (54.0, 114.6), (54.0, l2out[1])], 0.4, "BUCK5")
    r9g = _p(board, "R9", "2")
    r9c = _p(board, "R9", "1")
    # Continue up the gate pin's x to the row that already ties R8 and D6.
    t += wire([r9g, (gate4[0], r9g[1]), (gate4[0], r8g[1])], 0.25, "GATE4")
    q6c = _p(board, "Q6", "3")
    t += wire([q6c, (q6c[0], r9c[1]), r9c], 0.25, "Q6C")
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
